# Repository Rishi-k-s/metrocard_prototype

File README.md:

# MetroCard

A credit-card-sized PCB that shows real-time Kochi Metro data — a tiny, tappable transit map you can hold in your wallet.

Built by [Rishi Krishna](https://rishikrishna.com) / [Phenomi](https://phenomi.co). 

### Firmware
Checkout the metrocard [Firmware](https://github.com/Rishi-k-s/metrocard_firmware)

The schematic

## About

The front silkscreen traces the full Kochi Metro **Phase 1** line, from Aluva to Thripunithura, with every station labeled. A 1206 LED sits at each of the 49 stations (`D00`–`D48`), so the map can light up to reflect train position or other live status along the line.

The back houses the electronics:

- **U1 — HT16K33** LED driver/matrix controller, addressed over **I²C**
- **J1** — 4-pin JST-EH connector breaking out `GND`, `5V`, `SDA`, `SCL`
- **JP2/JP3** — address jumpers (`A0`, `A1`) so multiple cards can share an I²C bus at different addresses
- **JP4/JP5** — I²C bus pass-through/jumpers
- Pull-up resistors and support passives for the I²C bus and driver

The card is standard credit-card dimensions, designed to be carried like any other card.

## Credits

- Metro map artwork inspired by Saneef Ansari
- Station and line data provided by Kochi Metro Rail Limited (KMRL)

## Repository contents

- `metrocard.kicad_pro` / `metrocard.kicad_pcb` / `metrocard.kicad_sch` — KiCad project, PCB layout, and schematic
- `metrocard.csv` — bill of materials
- `DRC.rpt` — latest design rule check report
- `images/` — renders/screenshots of the board
- `libs/`, `fp-lib-table`, `sym-lib-table` — local footprint/symbol library references

## Status

Revision 0.1 — first prototype (`Rev 0.1 | P1 060108026001`).

## License

Open source hardware, licensed under the [GNU GPL v3](LICENSE.md).

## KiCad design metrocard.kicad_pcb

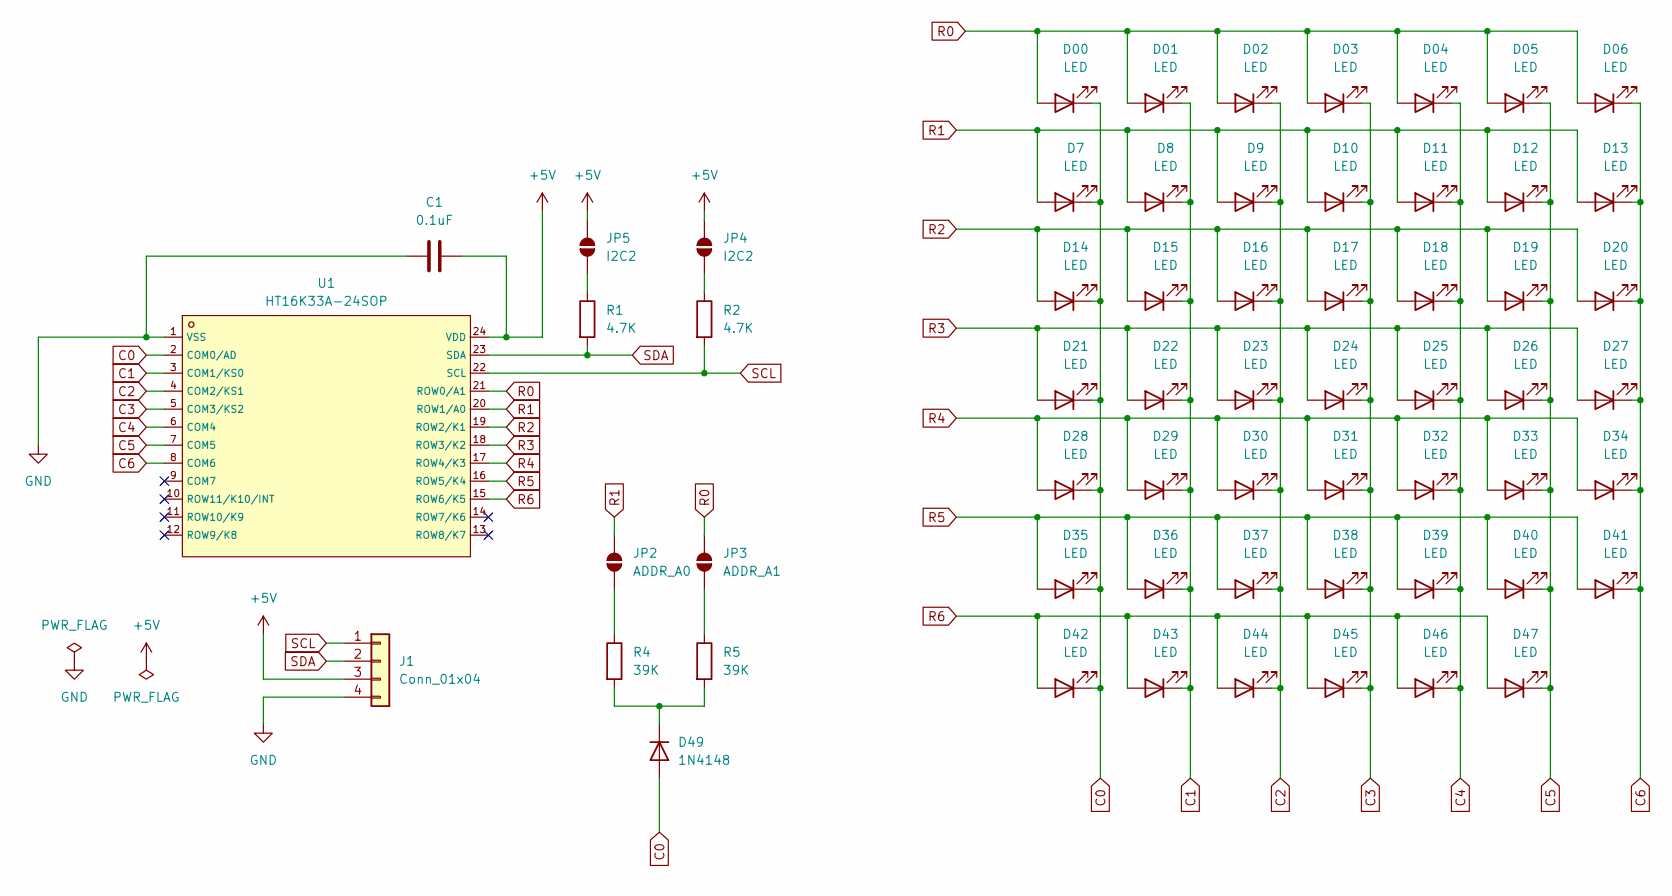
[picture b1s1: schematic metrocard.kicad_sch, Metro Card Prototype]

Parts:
C1: 0.1uF; C_1206_3216Metric
D00, D01, D02, D03, D04, D05, D06, D7, D8, D9, D10, D11, D12, D13, D14, D15, D16, D17, D18, D19, D20, D21, D22, D23, D24, D25, D26, D27, D28, D29, D30, D31, D32, D33, D34, D35, D36, D37, D38, D39, D40, D41, D42, D43, D44, D45, D46, D47: LED; LED_1206_3216Metric
D49: 1N4148; D_DO-35_SOD27_P7.62mm_Horizontal
J1: Conn_01x04; JST_EH_B4B-EH-A_1x04_P2.50mm_Vertical
JP2: ADDR_A0; SolderJumper-2_P1.3mm_Open_TrianglePad1.0x1.5mm
JP3: ADDR_A1; SolderJumper-2_P1.3mm_Open_TrianglePad1.0x1.5mm
JP4, JP5: I2C2; SolderJumper-2_P1.3mm_Open_TrianglePad1.0x1.5mm
R1, R2: 4.7K; R_1206_3216Metric
R4, R5: 39K; R_1206_3216Metric
U1: HT16K33A-24SOP; C5444735_SOP-24_L15_4-W7_5-P1_27-LS10_4-BL; LCSC C5444735

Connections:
+5V: C1.2, J1.3, JP4.2 (B), JP5.2 (B), U1.24 (VDD)
C0: D00.1 (K), D7.1 (K), D14.1 (K), D21.1 (K), D28.1 (K), D35.1 (K), D42.1 (K), D49.2 (A), U1.2 (COM0/AD)
C1: D01.1 (K), D8.1 (K), D15.1 (K), D22.1 (K), D29.1 (K), D36.1 (K), D43.1 (K), U1.3 (COM1/KS0)
C2: D02.1 (K), D9.1 (K), D16.1 (K), D23.1 (K), D30.1 (K), D37.1 (K), D44.1 (K), U1.4 (COM2/KS1)
C3: D03.1 (K), D10.1 (K), D17.1 (K), D24.1 (K), D31.1 (K), D38.1 (K), D45.1 (K), U1.5 (COM3/KS2)
C4: D04.1 (K), D11.1 (K), D18.1 (K), D25.1 (K), D32.1 (K), D39.1 (K), D46.1 (K), U1.6 (COM4)
C5: D05.1 (K), D12.1 (K), D19.1 (K), D26.1 (K), D33.1 (K), D40.1 (K), D47.1 (K), U1.7 (COM5)
C6: D06.1 (K), D13.1 (K), D20.1 (K), D27.1 (K), D34.1 (K), D41.1 (K), U1.8 (COM6)
GND: C1.1, J1.4, U1.1 (VSS)
unnamed: D49.1 (K), R4.2, R5.2
unnamed: JP2.1 (A), R4.1
unnamed: JP3.1 (A), R5.1
unnamed: JP4.1 (A), R2.1
unnamed: JP5.1 (A), R1.1
R0: D00.2 (A), D01.2 (A), D02.2 (A), D03.2 (A), D04.2 (A), D05.2 (A), D06.2 (A), JP3.2 (B), U1.21 (ROW0/A1)
R1: D7.2 (A), D8.2 (A), D9.2 (A), D10.2 (A), D11.2 (A), D12.2 (A), D13.2 (A), JP2.2 (B), U1.20 (ROW1/A0)
R2: D14.2 (A), D15.2 (A), D16.2 (A), D17.2 (A), D18.2 (A), D19.2 (A), D20.2 (A), U1.19 (ROW2/K1)
R3: D21.2 (A), D22.2 (A), D23.2 (A), D24.2 (A), D25.2 (A), D26.2 (A), D27.2 (A), U1.18 (ROW3/K2)
R4: D28.2 (A), D29.2 (A), D30.2 (A), D31.2 (A), D32.2 (A), D33.2 (A), D34.2 (A), U1.17 (ROW4/K3)
R5: D35.2 (A), D36.2 (A), D37.2 (A), D38.2 (A), D39.2 (A), D40.2 (A), D41.2 (A), U1.16 (ROW5/K4)
R6: D42.2 (A), D43.2 (A), D44.2 (A), D45.2 (A), D46.2 (A), D47.2 (A), U1.15 (ROW6/K5)
SCL: J1.1, R2.2, U1.22 (SCL)
SDA: J1.2, R1.2, U1.23 (SDA)

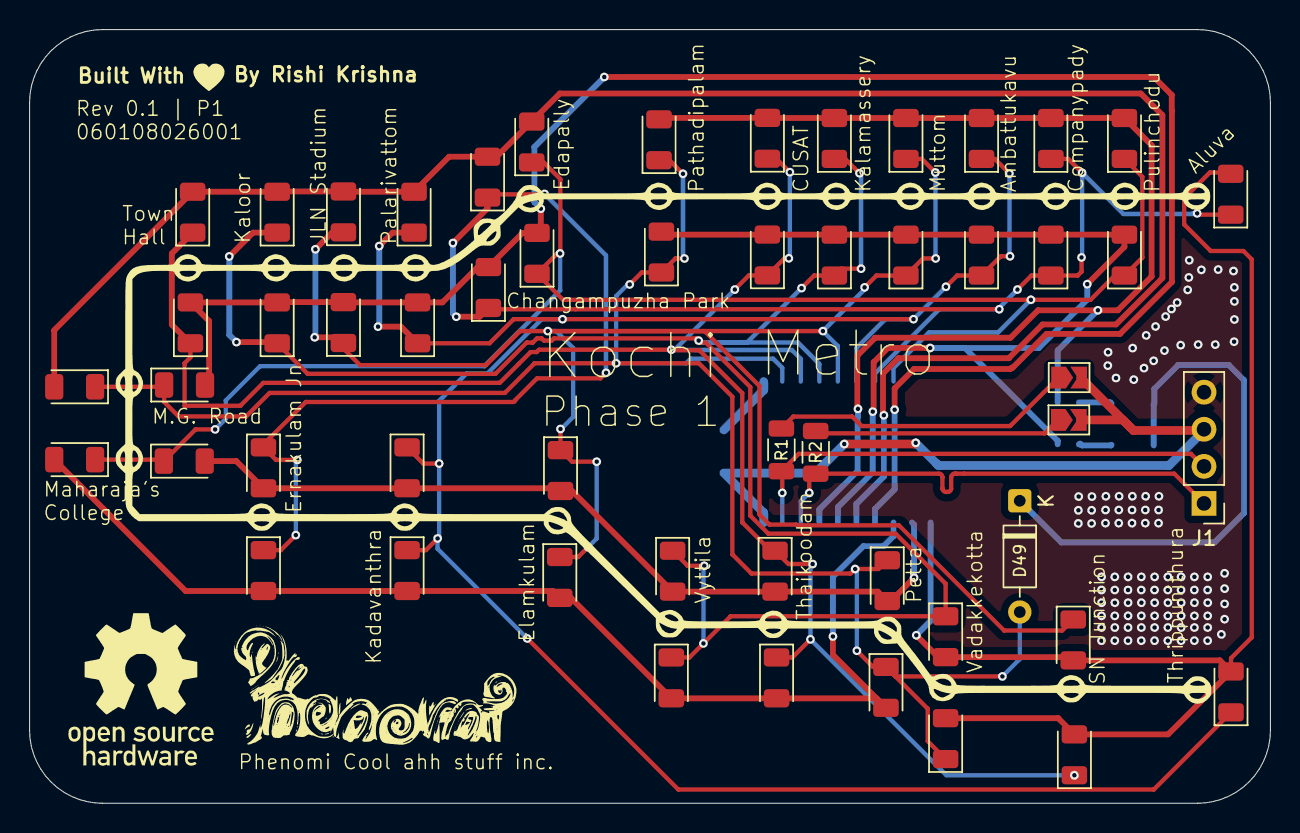
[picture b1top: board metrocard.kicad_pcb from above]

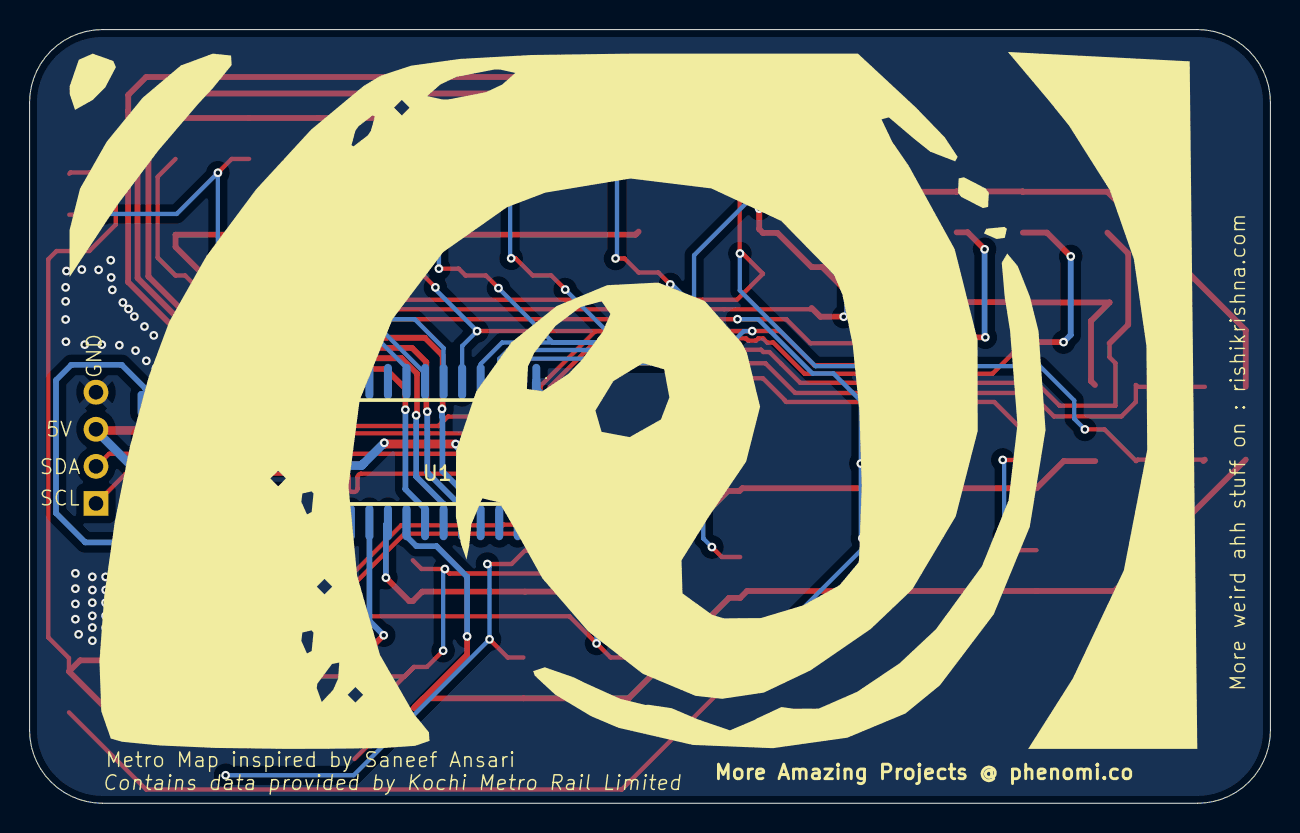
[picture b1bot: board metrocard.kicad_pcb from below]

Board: 2 copper layers, 85.0 x 53.0 mm, 60 parts (6 on the bottom side), 23 nets.
